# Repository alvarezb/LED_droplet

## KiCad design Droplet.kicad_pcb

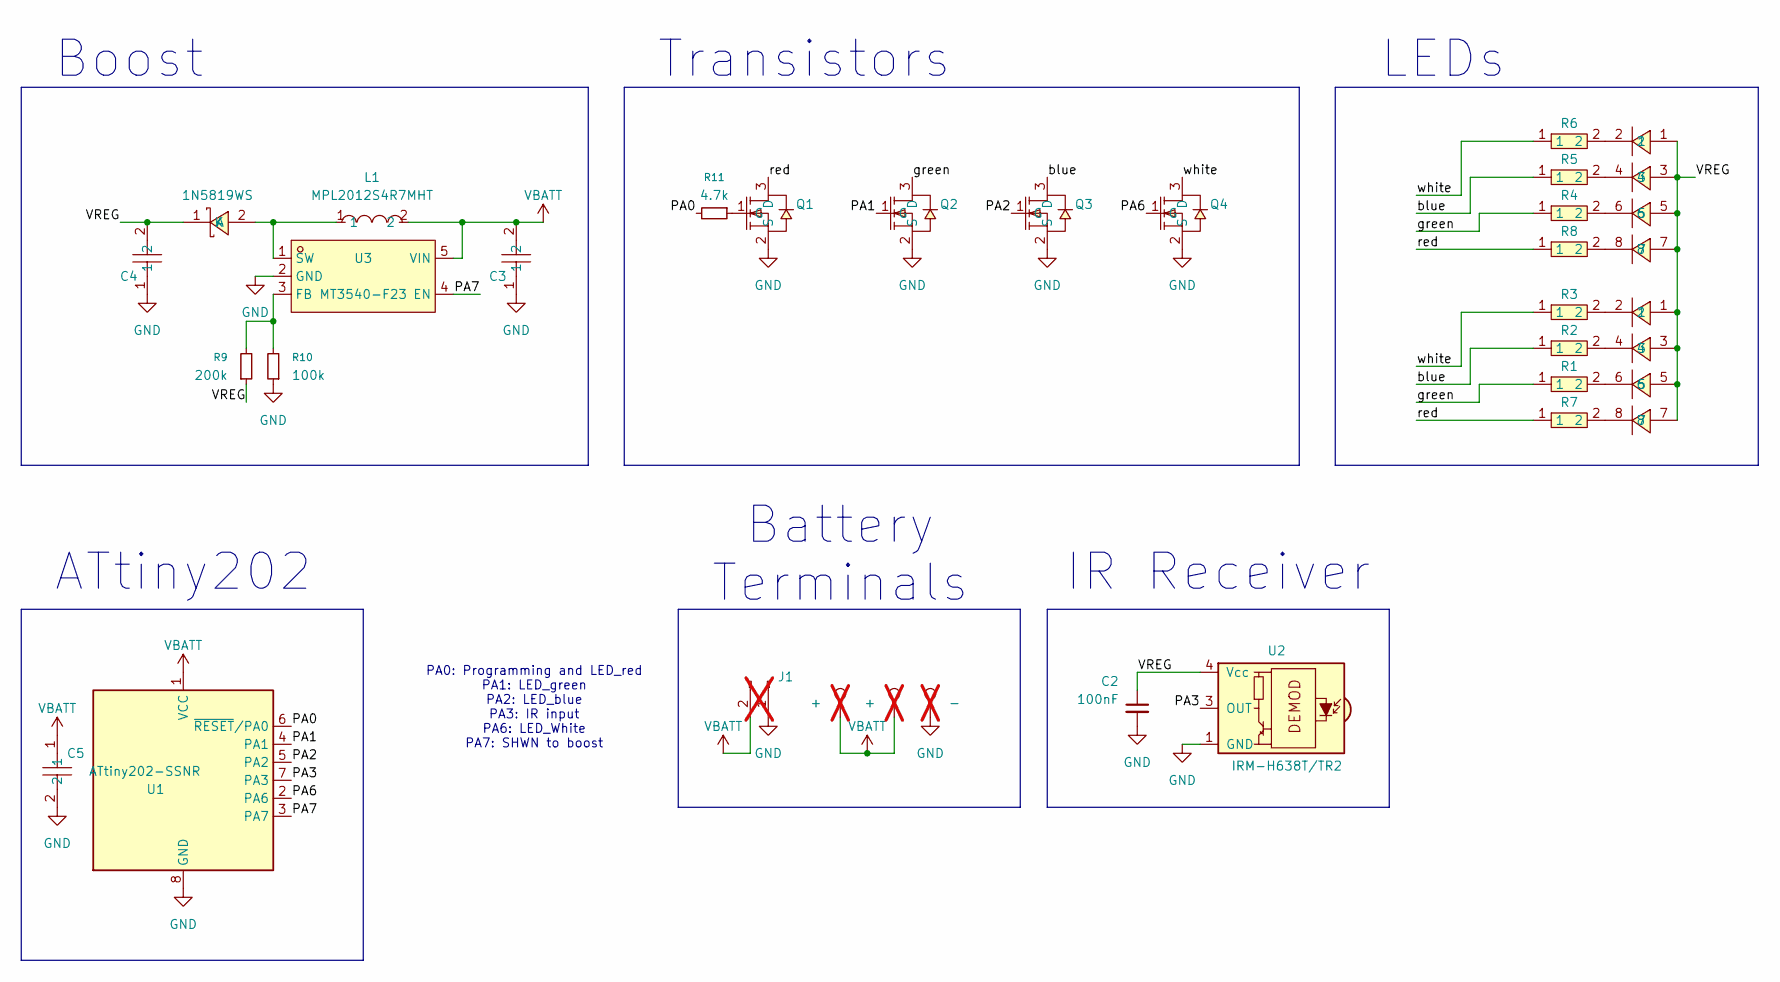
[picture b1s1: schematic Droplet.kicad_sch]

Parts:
C2: 100nF; C_0402_1005Metric; Voltage 1kV; Tolerance 100%
C3, C4, C5: CL05A475MP5NRNC; C0402; MPN CL05A475MP5NRNC; LCSC Part C23733
D1, D2: HL-5050RGBW-S1-A27; LED-SMD_8P-L5.0-W5.0-P1.20_HL-5050RGBW-S1-A27; LCSC Part C22470444
D3: 1N5819WS; SOD-323_L1.8-W1.3-LS2.5-RD; MPN 1N5819WS; LCSC Part C191023
J1: Conn_01x02_Pin; PinHeader_1x02_P2.54mm_Vertical; not fitted
L1: MPL2012S4R7MHT; L0805; MPN MPL2012S4R7MHT; LCSC Part C63166
Q1, Q2, Q3, Q4: BSS138W_C28646265; SOT-323-3_L2.1-W1.3-P1.30-LS2.3-BR; MPN BSS138W; LCSC Part C28646265
R1, R2, R3, R4, R5, R6: 0402WGF1502TCE; R0402; MPN 0402WGF1502TCE; LCSC Part C25756
R7, R8: 0402WGF4702TCE; R0402; MPN 0402WGF4702TCE; LCSC Part C25792
R9: 200k; R_0402_1005Metric
R10: 100k; R_0402_1005Metric
R11: 4.7k; R_0402_1005Metric
TP1: +; TestPoint_Pad_D6.0mm; not fitted
TP2: -; TestPoint_Pad_D6.0mm; not fitted
TP3: +; TestPoint_Pad_D2.0mm; not fitted
U1: ATtiny202-SSNR; SOIC-8_3.9x4.9mm_P1.27mm
U2: IRM-H638T/TR2; Everlight_IRM-H6xxT
U3: MT3540-F23; SOT-23-5_L3.0-W1.7-P0.95-LS2.8-BR; MPN MT3540-F23; LCSC Part C181783

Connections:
/PA0: R11.2, U1.6 (~RESET/PA0)
/PA1: Q2.1 (G), U1.4 (PA1)
/PA2: Q3.1 (G), U1.5 (PA2)
/PA3: U1.7 (PA3), U2.3 (OUT)
/PA6: Q4.1 (G), U1.2 (PA6)
/PA7: U1.3 (PA7), U3.4 (EN)
/VREG: C2.1, C4.2, D1.1, D1.3, D1.5, D1.7, D2.1, D2.3, D2.5, D2.7, D3.1 (K), R9.1, U2.4 (Vcc)
/blue: Q3.3 (D), R2.1, R5.1
/green: Q2.3 (D), R1.1, R4.1
/red: Q1.3 (D), R7.1, R8.1
/white: Q4.3 (D), R3.1, R6.1
GND: C2.2, C3.1, C4.1, C5.2, J1.1, Q1.2 (S), Q2.2 (S), Q3.2 (S), Q4.2 (S), R10.1, TP2.1 (1_1), U1.8 (GND), U2.1 (GND), U2.2 (GND), U3.2 (GND)
unnamed: D1.2, R6.2
unnamed: D1.4, R5.2
unnamed: D1.6, R4.2
unnamed: D1.8, R8.2
unnamed: D2.2, R3.2
unnamed: D2.4, R2.2
unnamed: D2.6, R1.2
unnamed: D2.8, R7.2
unnamed: D3.2 (A), L1.1, U3.1 (SW)
unnamed: Q1.1 (G), R11.1
unnamed: R9.2, R10.2, U3.3 (FB)
VBATT: C3.2, C5.1, J1.2, L1.2, TP1.1 (1_1), TP3.1 (1_1), U1.1 (VCC), U3.5 (VIN)

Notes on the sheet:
ATtiny202
Transistors
Battery Terminals
LEDs
IR Receiver
Boost
PA0: Programming and LED_red PA1: LED_green PA2: LED_blue PA3: IR input PA6: LED_White PA7: SHWN to boost

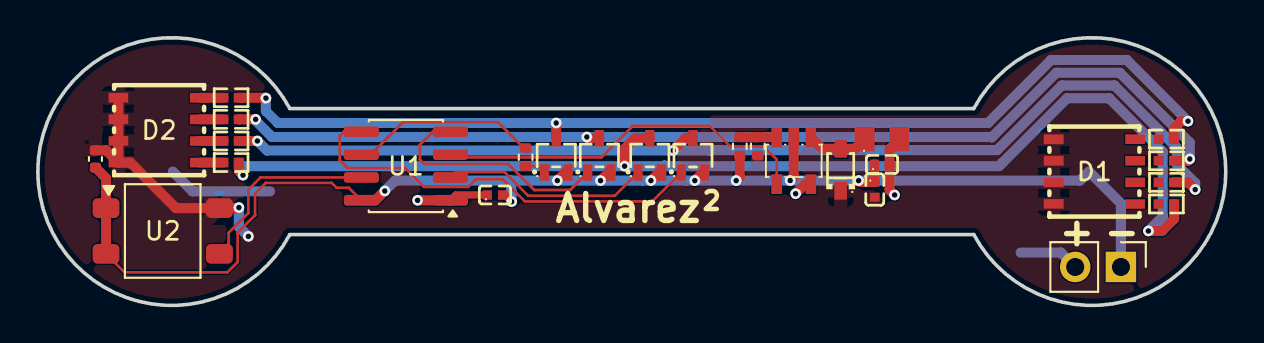
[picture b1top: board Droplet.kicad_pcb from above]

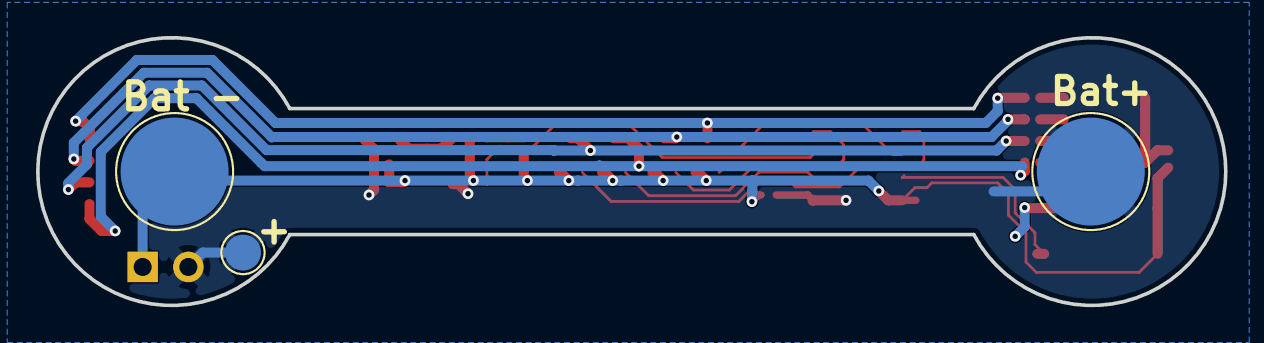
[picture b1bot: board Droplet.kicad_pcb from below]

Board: 2 copper layers, 66.0 x 14.9 mm, 30 parts (3 on the bottom side), 24 nets.

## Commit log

2025-12-11 initial commit, before fancy cuts
2025-12-12 do layout, including mouse bites
2025-12-12 update to use warm white RGB LED. Single unit layout
2025-12-15 rework with castellated connectors
2025-12-16 update schematic readability, rotate ir receiver
2025-12-17 update output files
2025-12-17 add larger battery terminal
2025-12-17 10 LED pair panel
2026-04-28 major changes - add boost and mosfets
2026-05-06 add boost, rework for flex pcb, order
2026-05-11 First production run
